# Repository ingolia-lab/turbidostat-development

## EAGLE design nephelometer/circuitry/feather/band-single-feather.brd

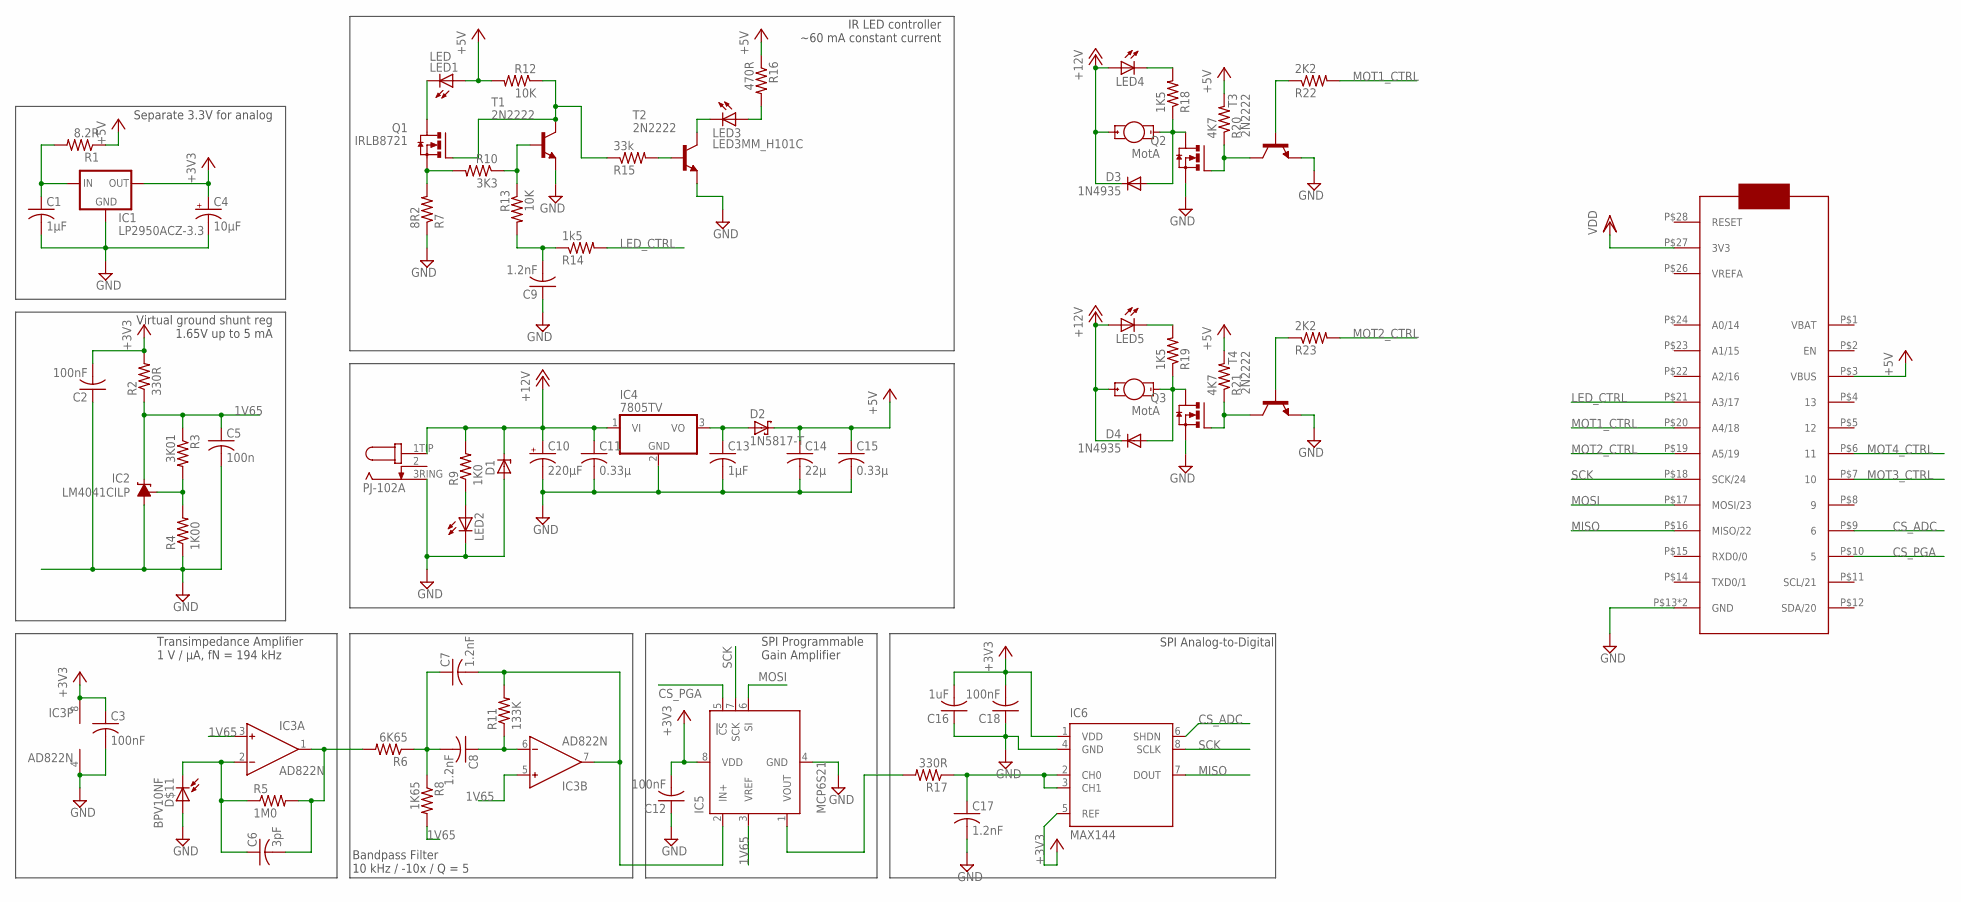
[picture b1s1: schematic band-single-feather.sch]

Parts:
C1, C13: 1µF; C025-030X050; DIGIKEY# 445-5318-ND
C2, C3, C12, C18: 100nF; C025-025X050; DIGIKEY# BC1084CT-ND
C4: 10µF; E2,5-5; DIGIKEY# 478-8042-1-ND
C5: 100n; C025-025X050; DIGIKEY# BC1084CT-ND
C6: 3pF; C025-024X044; DIGIKEY# 445-8377-ND
C7, C8, C9, C17: 1.2nF; C025-025X050; DIGIKEY# BC1026CT-ND
C10: 220µF; E3,5-8; DIGIKEY# P5166-ND
C11, C15: 0.33µ; C025-050X050; DIGIKEY# 445-5312-ND
C14: 22µ; C050-045X075; DIGIKEY# 445-8455-ND
C16: 1uF; C025-025X050; DIGIKEY# 445-5318-ND
D1: ZENER-DIODEF126-10; F126Z10; DIGIKEY# SA12ALFCT-ND
D2: 1N5817-T; DO41-7.6; DIGIKEY# 1N5817FSCT-ND
D3, D4: 1N4935; DO41-10; DIGIKEY# 1N4935FSCT-ND
D$11: BPV10NF; LED5MM; DIGIKEY# 751-1002-ND
IC1: LP2950ACZ-3.3; TO92; DIGIKEY# LP2950ACZ-3.3/NOPB-ND
IC2: LM4041CILP; LP_O-PBCY-W3; DIGIKEY# 296-22173-1-ND
IC3: AD822N; DIL08; DIGIKEY# AD823ANZ-ND
IC4: 7805TV; TO220V; DIGIKEY# LM7805CT-ND
IC5: MCP6S21; DIL08; DIGIKEY# MCP6S91-E/P-ND
IC6: MAX144; DIL08; DIGIKEY# MAX144ACPA+-ND
IC7: FEATHER_M0; DIGIKEY# 1528-1531-ND
J1: PJ-102A; DIGIKEY# CP-102A-ND
J2, J3: MotA; 1X02_3.5MM_MOT; DIGIKEY# ED2740-ND
LED1: LED; 1X02_3.5MM; DIGIKEY# 475-3002-ND
LED2: LED5MM; DIGIKEY# 754-1735-ND
LED3: LED3MM_H101C; DIGIKEY# 754-1727-ND
LED4, LED5: LED3MM; DIGIKEY# 754-1275-ND
Q1, Q2, Q3: IRLB8721; TO220BV; DIGIKEY# IRLB8721PBF-ND
R1: 8.2R; 0207/9; DIGIKEY# S8.2HCT-ND
R2: 330R; 0207/9; DIGIKEY# CF14JT330RCT-ND
R3: 3K01; 0207/9; DIGIKEY# RNF14FTD3K01CT-ND
R4: 1K00; 0207/9; DIGIKEY# RNF14FTD1K00CT-ND
R5: 1M0; 0207/9; DIGIKEY# RNV14FAL1M00CT-ND
R6: 6K65; 0207/9; DIGIKEY# 6.65KXBK-ND
R7: 8R2; 0207/9; DIGIKEY# S8.2HCT-ND
R8: 1K65; 0207/9; DIGIKEY# 1.65KXBK-ND
R9: 1K0; 0207/9; DIGIKEY# S1KHCT-ND
R10: 3K3; 0207/9; DIGIKEY# CF14JT3K30CT-ND
R11: 133K; 0207/9; DIGIKEY# 133KXBK-ND
R12, R13: 10K; 0207/9; DIGIKEY# CF14JT10K0CT-ND
R14: 1k5; 0207/9; DIGIKEY# CF14JT1K50CT-ND
R15: 33k; 0207/9; DIGIKEY# CF14JT33K0CT-ND
R16: 470R; 0207/5V; DIGIKEY# CF14JT470RCT-ND
R17: 330R; 0207/9; DIGIKEY# S330CACT-ND
R18, R19: 1K5; 0207/10; DIGIKEY# CF14JT1K50CT-ND
R20, R21: 4K7; 0207/10; DIGIKEY# CF14JT4K70CT-ND
R22, R23: 2K2; 0207/10; DIGIKEY# CF14JT2K20CT-ND
T1, T2, T3, T4: 2N2222; TO92-EBC-OVAL; DIGIKEY# PN2222ATFCT-ND

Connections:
1V65: C5.1, IC2.2 (C), IC3.3 (IN+), IC3.5 (IN+), IC5.3 (VREF), R2.1, R3.1, R8.2
+3V3: C2.2, C3.1, C4.+, C12.2, C16.2, C18.2, IC1.1 (OUT), IC3.8 (V+), IC5.8 (VDD), IC6.1 (VDD), IC6.5 (REF), R2.2
+5V: C14.1, C15.1, D2.C, IC7.P$3 (VBUS), LED1.1A (A), R1.1, R12.2, R16.1, R20.2, R21.2
+12V: C10.+, C11.1, D1.C, D3.C, D4.C, IC4.1 (VI), J1.1TIP (3TIP), J2.1A (+), J3.1A (+), LED4.A, LED5.A, R9.2
BPF: C7.2, IC3.7 (OUT), IC5.2 (IN+), R11.2
CS_ADC: IC6.6 (SHDN), IC7.P$9 (6)
CS_PGA: IC5.5 (!CS), IC7.P$10 (5)
FB: C6.1, D$11.K, IC3.2 (IN-), R5.1
GND: C1.2, C2.1, C3.2, C4.-, C5.2, C9.1, C10.-, C11.2, C12.1, C13.2, C14.2, C15.2, C16.1, C17.2, C18.1, D1.A, D$11.A, IC1.2 (GND), IC2.3 (A), IC3.4 (V-), IC4.2 (GND), IC5.4 (GND), IC6.4 (GND), IC7.P$13 (GND), IC7.P$25 (GND), J1.3RING (1RING), LED2.K (C), Q2.S, Q3.S, R4.1, R7.1, T1.E, T2.E, T3.E, T4.E
LED_CTRL: IC7.P$21 (A3/17), R14.2
MISO: IC6.7 (DOUT), IC7.P$16 (MISO/22)
MOSI: IC5.6 (SI), IC7.P$17 (MOSI/23)
MOT1: Q2.G, R20.1, T3.C
MOT1_CTRL: IC7.P$20 (A4/18), R22.2
MOT2: Q3.G, R21.1, T4.C
MOT2_CTRL: IC7.P$19 (A5/19), R23.2
MOT3_CTRL: IC7.P$7 (10)
MOT4_CTRL: IC7.P$6 (11)
unnamed: LED2.A, R9.1
unnamed: C7.1, C8.2, R6.1, R8.1
unnamed: IC5.1 (VOUT), R17.2
unnamed: D3.A, J2.2K (-), Q2.D, R18.1
unnamed: LED4.K (C), R18.2
unnamed: R22.1, T3.B
unnamed: Q1.G, R12.1, R15.1, T1.C
unnamed: C8.1, IC3.6 (IN-), R11.1
unnamed: D4.A, J3.2K (-), Q3.D, R19.1
unnamed: LED3.A, R16.2
unnamed: LED3.K, T2.C
unnamed: R10.1, R13.1, T1.B
unnamed: Q1.S, R7.2, R10.2
unnamed: C9.2, R13.2, R14.1
unnamed: R15.2, T2.B
unnamed: LED1.2K (K), Q1.D
unnamed: LED5.K (C), R19.2
unnamed: R23.1, T4.B
unnamed: C13.1, D2.A, IC4.3 (VO)
unnamed: C17.1, IC6.2 (CH0), IC6.3 (CH1), R17.1
unnamed: C1.1, IC1.3 (IN), R1.2
unnamed: IC2.1 (FB), R3.2, R4.2
SCK: IC5.7 (SCK), IC6.8 (SCLK), IC7.P$18 (SCK/24)
TIA: C6.2, IC3.1 (OUT), R5.2, R6.2
VDD: IC7.P$27 (3V3)

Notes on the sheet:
Transimpedance Amplifier 1 V / µA, fN = 194 kHz
Bandpass Filter 10 kHz / -10x / Q = 5
Virtual ground shunt reg 1.65V up to 5 mA
IR LED controller ~60 mA constant current
SPI Programmable Gain Amplifier
Separate 3.3V for analog
SPI Analog-to-Digital

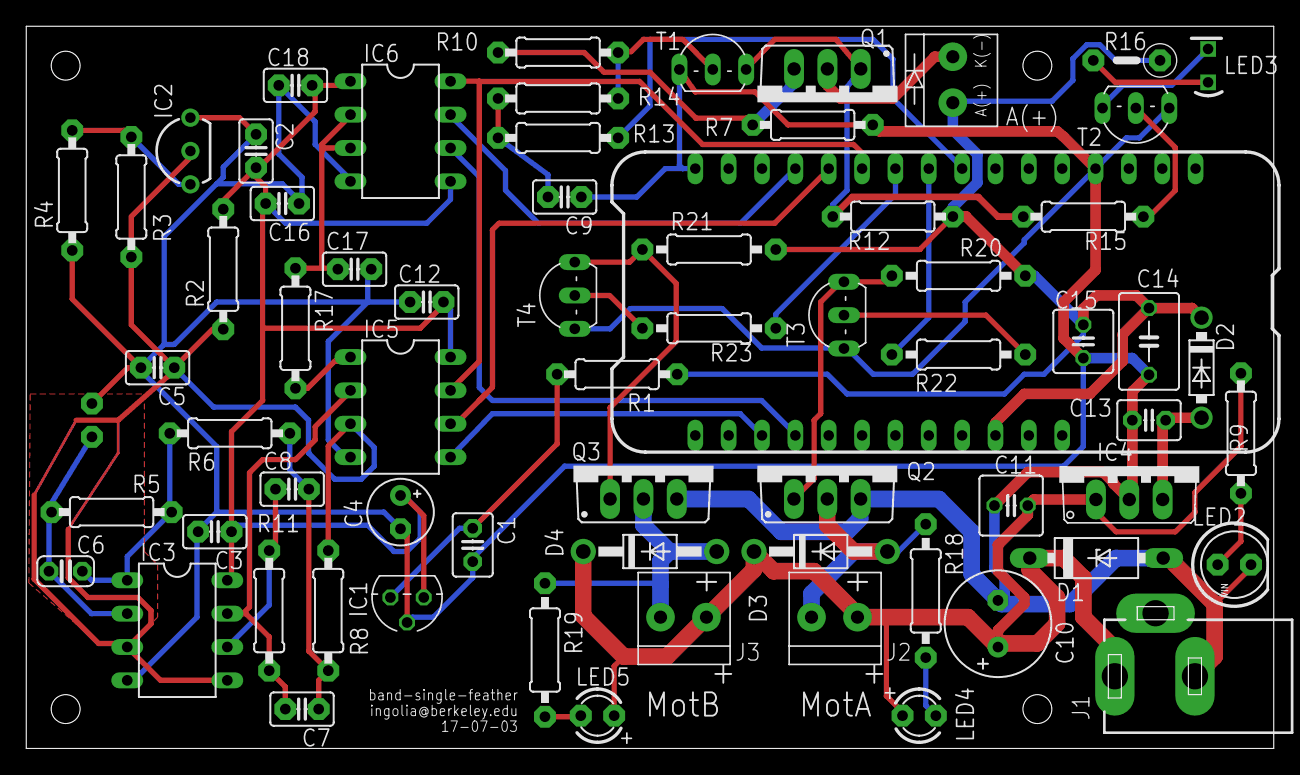
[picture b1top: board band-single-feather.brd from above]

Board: 2 copper layers, 95.0 x 55.0 mm, 72 parts (1 on the bottom side), 40 nets.

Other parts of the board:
U$1, U$2, U$3, U$4: M2MOUNT

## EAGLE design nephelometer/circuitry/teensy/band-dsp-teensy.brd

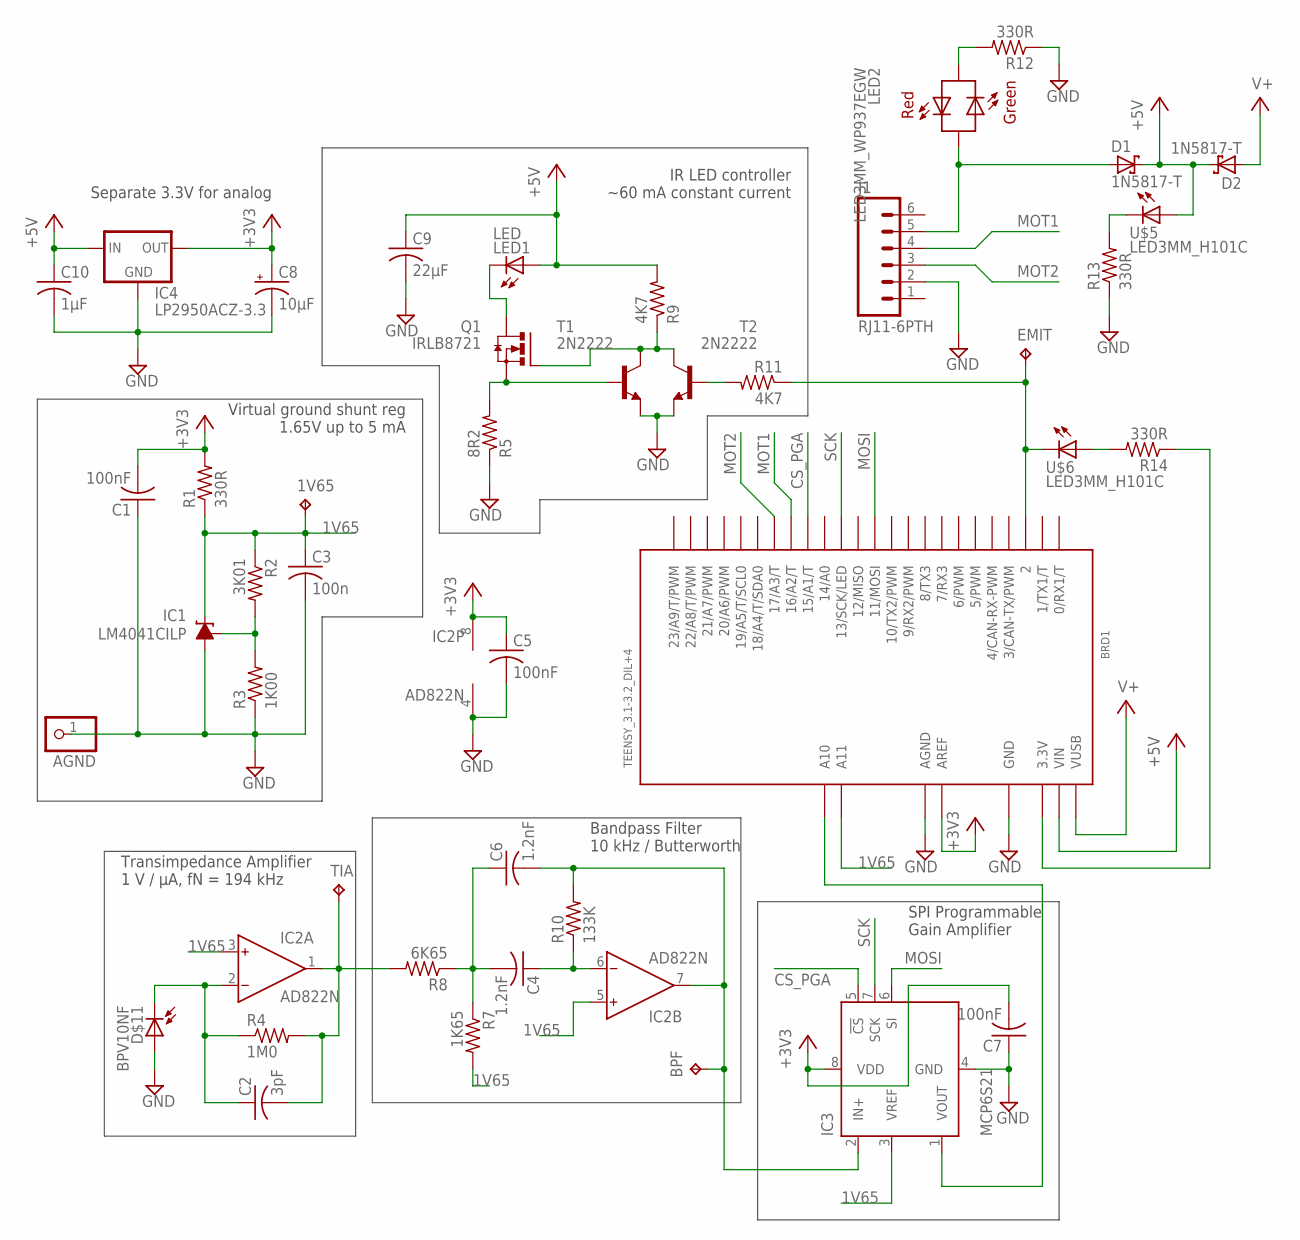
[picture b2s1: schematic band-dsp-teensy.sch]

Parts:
1V65: TPTP10R; TP10R
AGND: PINHD-1X1; 1X01
BPF: TPTP10R; TP10R
BRD1: TEENSY_3.1-3.2_DIL+4; TEENSY_3.0-3.2&LC_DIL+4; DIGIKEY# 1568-1231-ND
C1, C5, C7: 100nF; C025-025X050; DIGIKEY# BC1084CT-ND
C2: 3pF; C025-024X044; DIGIKEY# 445-8377-ND
C3: 100n; C025-025X050; DIGIKEY# BC1084CT-ND
C4, C6: 1.2nF; C025-025X050; DIGIKEY# BC1026CT-ND
C8: 10µF; E2,5-5; DIGIKEY# 478-8042-1-ND
C9: 22µF; C050-045X075; DIGIKEY# 445-8455-ND
C10: 1µF; C025-030X050; DIGIKEY# 445-5318-ND
D1, D2: 1N5817-T; DO41-7.6; DIGIKEY# 1N5817FSCT-ND
D$11: BPV10NF; LED5MM; DIGIKEY# 751-1002-ND
EMIT: TPPAD1-13; P1-13
IC1: LM4041CILP; LP_O-PBCY-W3; DIGIKEY# 296-22173-1-ND
IC2: AD822N; DIL08; DIGIKEY# AD823ANZ-ND
IC3: MCP6S21; DIL08; DIGIKEY# MCP6S91-E/P-ND
IC4: LP2950ACZ-3.3; TO92; DIGIKEY# LP2950ACZ-3.3/NOPB-ND
J1: RJ11-6PTH; RJ11-6; DIGIKEY# AE10383-ND
LED1: LED; 1X02_3.5MM; DIGIKEY# 475-3002-ND
LED2: LED3MM_WP937EGW; LED3MM_H101C_BICOL; DIGIKEY# 754-1751-ND
Q1: IRLB8721; TO220BH; DIGIKEY# IRLB8721PBF-ND
R1, R12, R13: 330R; 0207/9; DIGIKEY# CF14JT330RCT-ND
R2: 3K01; 0207/9; DIGIKEY# RNF14FTD3K01CT-ND
R3: 1K00; 0207/9; DIGIKEY# RNF14FTD1K00CT-ND
R4: 1M0; 0207/9; DIGIKEY# RNV14FAL1M00CT-ND
R5: 8R2; 0207/9; DIGIKEY# S8.2HCT-ND
R7: 1K65; 0207/9; DIGIKEY# 1.65KXBK-ND
R8: 6K65; 0207/9; DIGIKEY# 6.65KXBK-ND
R9, R11: 4K7; 0207/9; DIGIKEY# CF14JT4K70CT-ND
R10: 133K; 0207/9; DIGIKEY# 133KXBK-ND
R14: 330R; 0207/9; DIGIKEY# CF14JT150RCT-ND
T1, T2: 2N2222; TO92-EBC-OVAL; DIGIKEY# PN2222ATFCT-ND
TIA: TPTP10R; TP10R
U$5: LED3MM_H101C; DIGIKEY# 754-1595-ND
U$6: LED3MM_H101C; DIGIKEY# 754-1727-ND

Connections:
1V65: 1V65.TP, BRD1.A11, C3.1, IC1.2 (C), IC2.3 (IN+), IC2.5 (IN+), IC3.3 (VREF), R1.1, R2.1, R7.2
+3V3: BRD1.AREF, C1.2, C5.1, C7.2, C8.+, IC2.8 (V+), IC3.8 (VDD), IC4.1 (OUT), R1.2
+5V: BRD1.VIN, C9.1, C10.1, D1.C, D2.C, IC4.3 (IN), LED1.1A (A), R9.2, U$5.A
CS_PGA: BRD1.15/A1 (15/A1/T), IC3.5 (!CS)
GND: AGND.1, BRD1.AGND, BRD1.GND, C1.1, C3.2, C5.2, C7.1, C8.-, C9.2, C10.2, D$11.A, IC1.3 (A), IC2.4 (V-), IC3.4 (GND), IC4.2 (GND), J1.2, R3.1, R5.1, R12.1, R13.1, T1.E, T2.E
LEDCTRL: R11.2, T2.B
MOSI: BRD1.11 (11/MOSI), IC3.6 (SI)
MOT1: BRD1.16/A2 (16/A2/T), J1.4
MOT2: BRD1.17/A3 (17/A3/T), J1.3
unnamed: C2.1, D$11.K, IC2.2 (IN-), R4.1
unnamed: BRD1.3.3V, R14.1
unnamed: C4.2, C6.1, R7.1, R8.1
unnamed: BRD1.A10, IC3.1 (VOUT)
unnamed: BRD1.2, EMIT.TP, R11.1, U$6.K
unnamed: BPF.TP, C6.2, IC2.7 (OUT), IC3.2 (IN+), R10.2
unnamed: R13.2, U$5.K
unnamed: Q1.G, R9.1, T1.C, T2.C
unnamed: C4.1, IC2.6 (IN-), R10.1
unnamed: D1.A, J1.5, LED2.SHORT (GA)
unnamed: R14.2, U$6.A
unnamed: LED2.LONG (GK), R12.2
unnamed: Q1.S, R5.2, T1.B
unnamed: LED1.2K (K), Q1.D
unnamed: C2.2, IC2.1 (OUT), R4.2, R8.2, TIA.TP
unnamed: IC1.1 (FB), R2.2, R3.2
SCK: BRD1.13 (13/SCK/LED), IC3.7 (SCK)
V+: BRD1.VUSB, D2.A

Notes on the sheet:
Transimpedance Amplifier 1 V / µA, fN = 194 kHz
Bandpass Filter 10 kHz / Butterworth
Virtual ground shunt reg 1.65V up to 5 mA
IR LED controller ~60 mA constant current
SPI Programmable Gain Amplifier
Separate 3.3V for analog

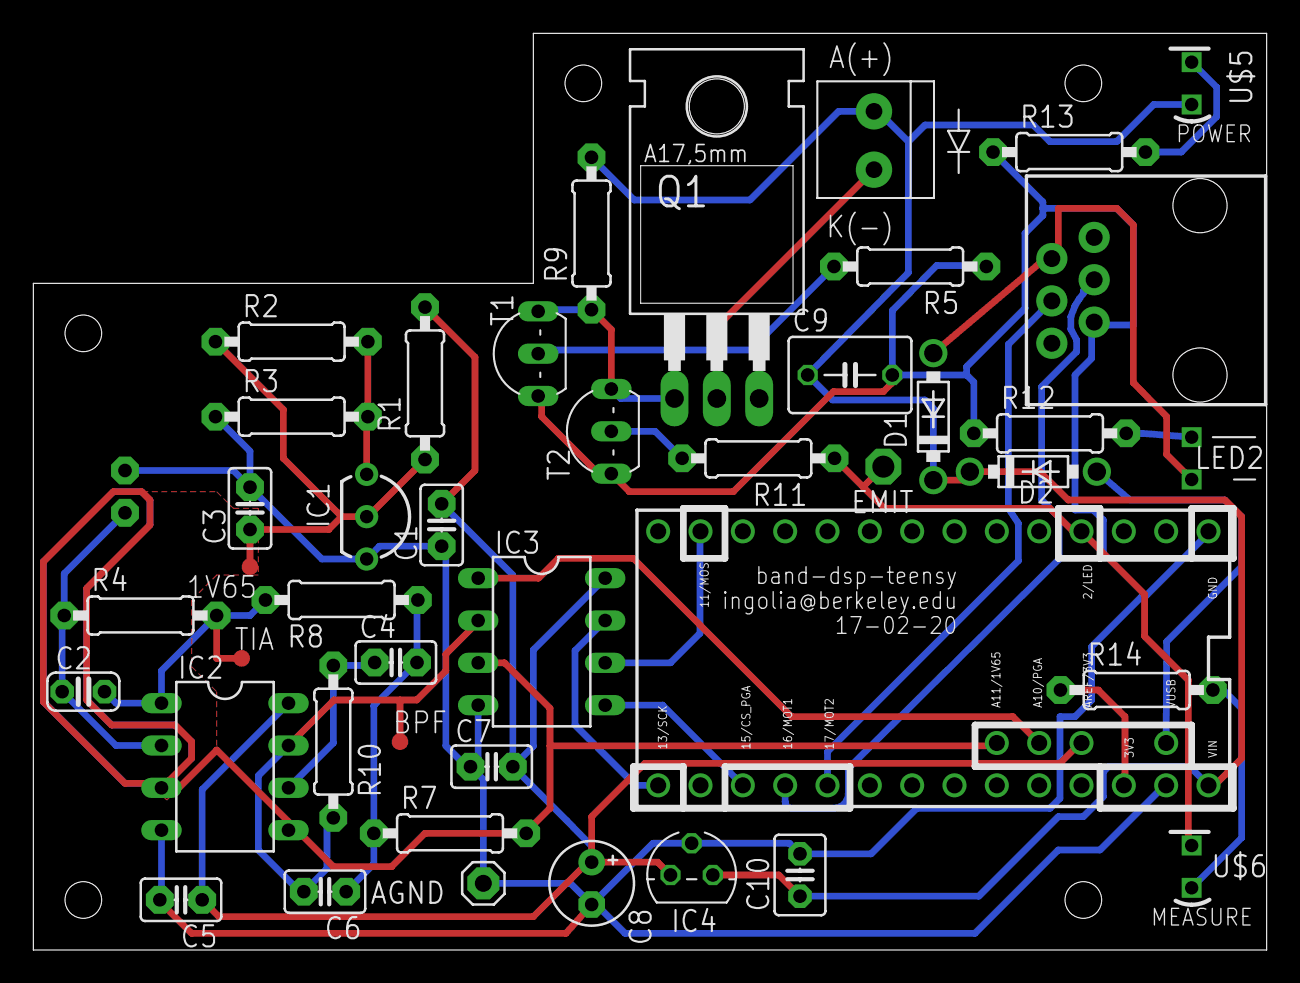
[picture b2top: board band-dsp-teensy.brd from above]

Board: 2 copper layers, 74.0 x 55.0 mm, 49 parts (1 on the bottom side), 27 nets.

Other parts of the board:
U$1, U$2, U$3, U$4, U$7: M2MOUNT

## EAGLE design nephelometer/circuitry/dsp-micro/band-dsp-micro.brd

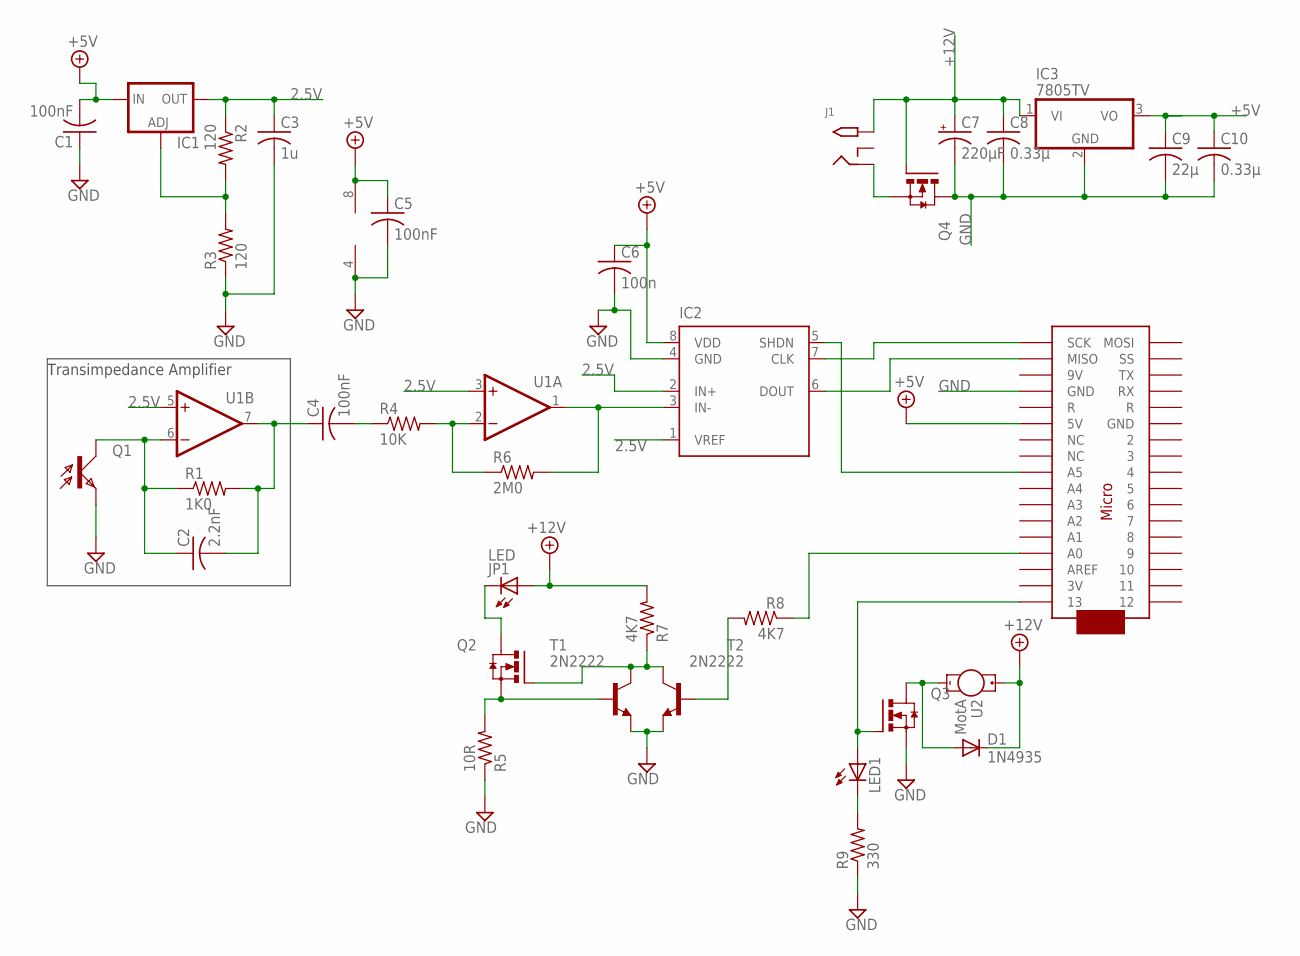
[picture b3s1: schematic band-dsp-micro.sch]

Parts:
C1, C5: 100nF; C025-025X050; DIGIKEY# BC1084CT-ND
C2: 2.2nF; C025-024X044; DIGIKEY# BC1029CT-ND
C3: 1u; C050-024X044; DIGIKEY# 445-8614-ND
C4: 100nF; C025-060X050; DIGIKEY# 445-8325-ND
C6: 100n; C025-025X050; DIGIKEY# BC1084CT-ND
C7: 220µF; E3,5-8; DIGIKEY# P5166-ND
C8, C10: 0.33µ; C025-050X050; DIGIKEY# 445-5312-ND
C9: 22µ; C050-045X075; DIGIKEY# 445-8455-ND
D1: 1N4935; DO41-10; DIGIKEY# 1N4935FSCT-ND
IC1: LM317L; 317L; DIGIKEY# 296-33312-5-ND
IC2: MCP3301; DIL08; DIGIKEY# MCP3301-BI/P-ND
IC3: 7805TV; TO220V; DIGIKEY# LM7805CT-ND
J1: 2.1MMJACKTHM; PJ-102A; DIGIKEY# CP-102A-ND
JP1: LED; 1X02_SCREW; DIGIKEY# 475-3002-ND
LED1: LED3MM; DIGIKEY# 160-1139-ND
Q1: LTR-4206; 3MM_LED; DIGIKEY# 160-1030-ND
Q2, Q3, Q4: IRLB8721; TO220BV; DIGIKEY# IRLB8721PBF-ND
R1: 1K0; 0204/5; DIGIKEY# S1KCACT-ND
R2, R3: 120; 0204V; DIGIKEY# S120CACT-ND
R4: 10K; 0204/5; DIGIKEY# S10KCACT-ND
R5: 10R; 0204V; DIGIKEY# PPC10W-1CT-ND
R6: 2M0; 0309V; DIGIKEY# RNV14FAL2M00TB-ND
R7, R8: 4K7; 0204V; DIGIKEY# S4.7KQCT-ND
R9: 330; 0204V; DIGIKEY# CF14JT330RCT-ND
T1, T2: 2N2222; TO92-EBC-OVAL; DIGIKEY# PN2222ATFCT-ND
U1: LMC6482; DIL08; DIGIKEY# LMC6482AIN/NOPB-ND
U2: MotA; 1X02_SCREW; DIGIKEY# SC1455-ND
U3: ARDUINOMICRO; DIGIKEY# 1050-1066-ND

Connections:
2.5V: C3.1, IC1.2 (OUT), IC2.1 (VREF), IC2.2 (IN+), R2.1, U1.3 (+IN), U1.5 (+IN)
+5V: C1.2, C5.1, C6.1, C9.1, C10.1, IC1.3 (IN), IC2.8 (VDD), IC3.3 (VO), U1.8 (V+), U3.P$23 (5V)
+12V: C7.+, C8.1, D1.C, IC3.1 (VI), J1.TIP, JP1.1/POS (A), Q4.G, R7.2, U2.1/POS (+)
GND: C1.1, C3.2, C5.2, C6.2, C7.-, C8.2, C9.2, C10.2, IC2.4 (GND), IC3.2 (GND), Q1.A (E), Q3.S, Q4.D, R3.1, R5.1, R9.1, T1.E, T2.E, U1.4 (V-), U3.P$12 (GND)
LEDCTRL: R8.2, T2.B
unnamed: C2.1, Q1.K (C), R1.1, U1.6 (-IN)
unnamed: C4.2, R4.1
unnamed: D1.A, Q3.D, U2.2 (-)
unnamed: IC2.6 (DOUT), U3.P$19 (MISO)
unnamed: R8.1, U3.P$31 (A0)
unnamed: IC2.7 (CLK), U3.P$18 (SCK)
unnamed: IC2.5 (SHDN), U3.P$26 (A5)
unnamed: Q2.G, R7.1, T1.C, T2.C
unnamed: Q2.S, R5.2, T1.B
unnamed: LED1.K (C), R9.2
unnamed: JP1.2 (K), Q2.D
unnamed: LED1.A, Q3.G, U3.P$34 (13)
unnamed: C2.2, C4.1, R1.2, U1.7 (OUT)
unnamed: R4.2, R6.1, U1.2 (-IN)
unnamed: IC2.3 (IN-), R6.2, U1.1 (OUT)
unnamed: IC1.1 (ADJ), R2.2, R3.2
unnamed: J1.RING, Q4.S

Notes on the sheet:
Transimpedance Amplifier

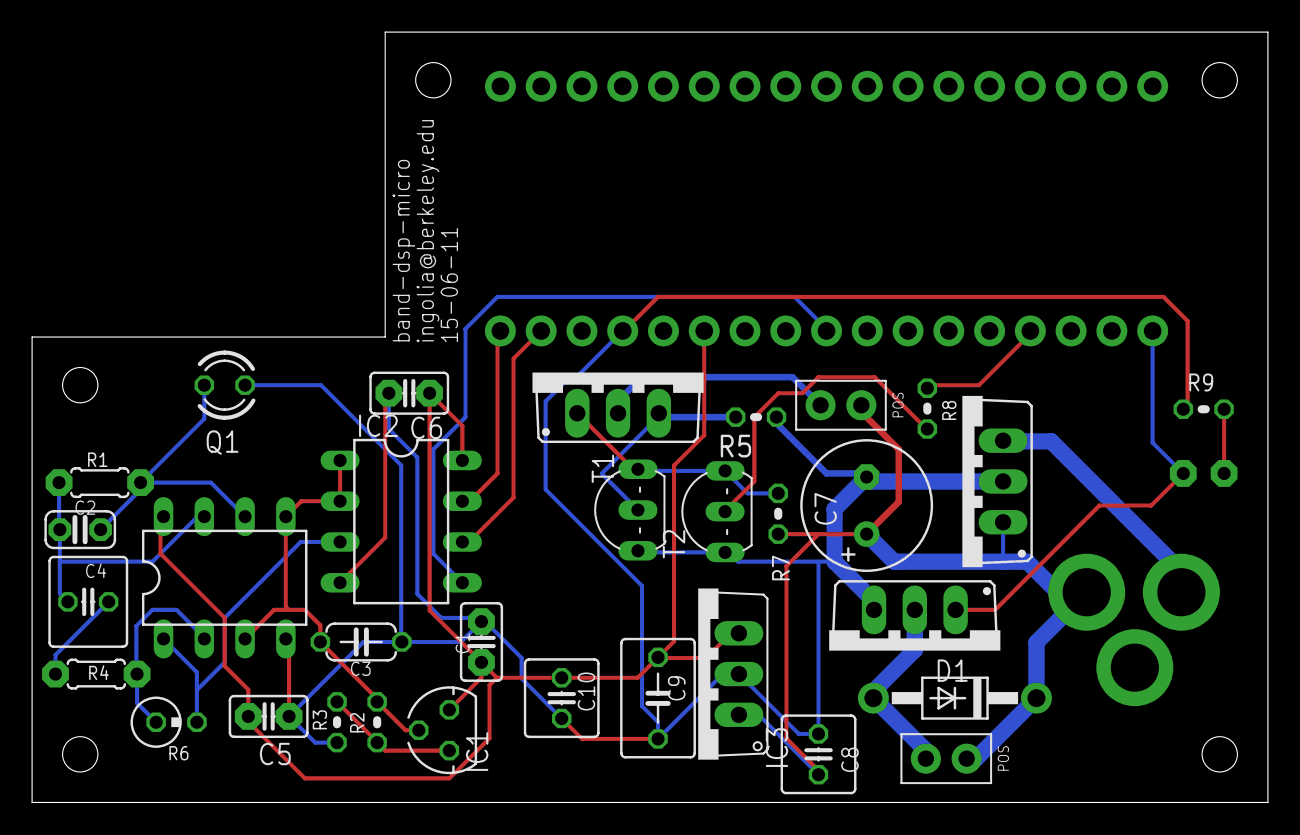
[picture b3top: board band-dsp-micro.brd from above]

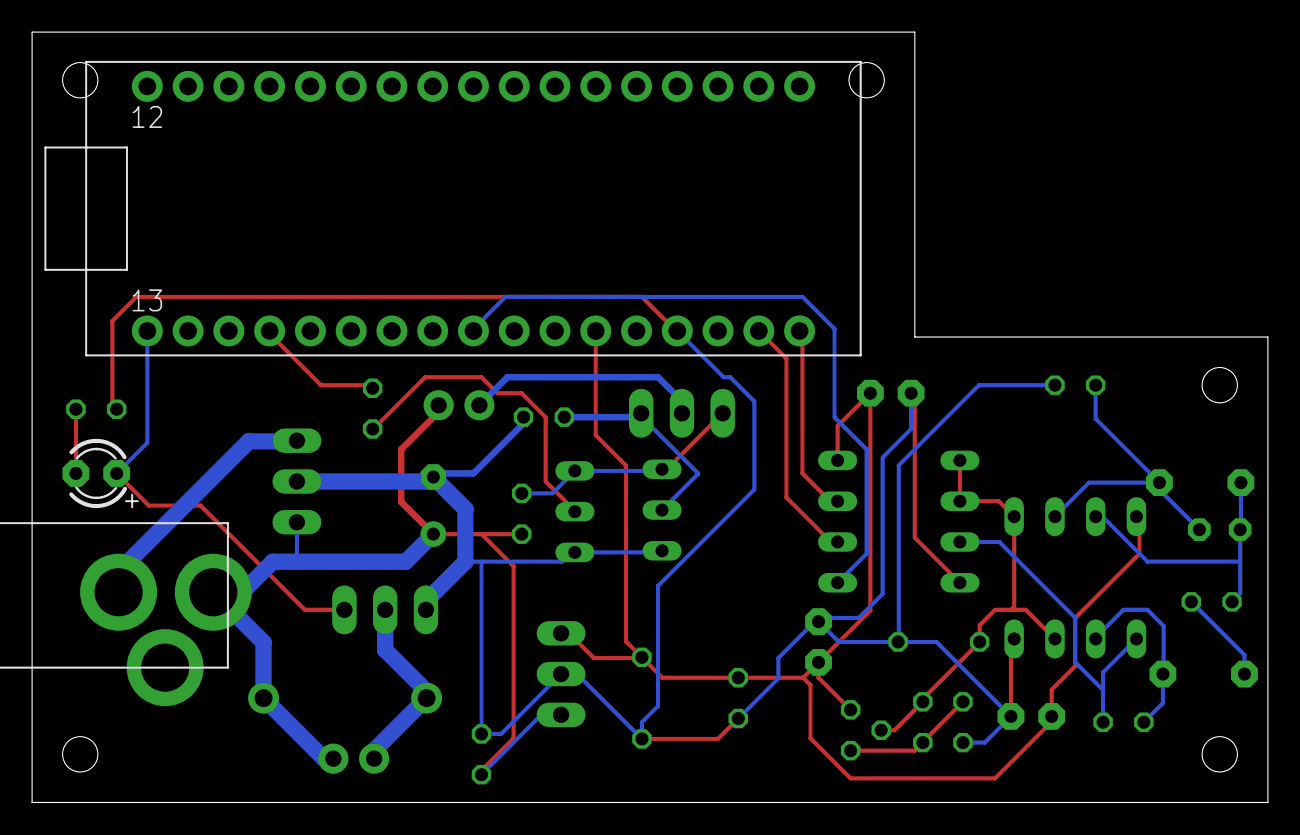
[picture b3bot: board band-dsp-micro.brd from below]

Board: 2 copper layers, 77.0 x 48.0 mm, 40 parts (3 on the bottom side), 22 nets.

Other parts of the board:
U$1, U$2, U$3, U$4, U$7: M2MOUNT

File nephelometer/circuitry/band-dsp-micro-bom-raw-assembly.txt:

C1	100nF	BC1084CT-ND	Vishay BC Components	K104K15X7RF5TL2
C2	2.2nF	BC1029CT-ND	Vishay BC Components	K222J15C0GF5TL2
C3	1u	445-8614-ND	TDK Corporation	FK28X7R1C105K
C4	100nF	445-8325-ND	TDK Corporation	FK16C0G1H104J
C5	100nF	BC1084CT-ND		
C6	100n	BC1084CT-ND		
C7	220µF	P5166-ND	Panasonic Electronic Components	ECA-1VM221
C8	0.33µ	445-5312-ND 	TDK Corporation	FK14X7R1H334K
C9	22µ	445-8455-ND	TDK Corporation	FK20X7R1C226M
C10	0.33µ	445-5312-ND 	TDK Corporation	FK14X7R1H334K
D1	1N4935	1N4935FSCT-ND	Fairchild Semiconductor	1N4935
IC1		296-33312-5-ND	Texas Instruments	LM317LCLP
IC2		MCP3301-BI/P-ND	Microchip Technology	MCP3301-BI/P
IC2		AE9986-ND		
IC3	7805TV	LM7805CT-ND 	Fairchild Semiconductor	LM7805CT
J1	2.1MMJACKTHM	CP-102A-ND 	CUI Inc	PJ-102A
J1	2.1MMJACKTHM	T1071-P5P-ND 	CUI Inc	EPSA120200U-P5P-SZ
JP1	LED	475-3002-ND	OSRAM Opto Semiconductors Inc	SFH 4547
JP1	LED	492-1502-ND	Bivar Inc	CR-174
LED1		160-1139-ND	Lite-On Inc	LTL-4221N
Q1		160-1030-ND	Lite-On Inc	LTR-4206E
Q2		IRLB8721PBF-ND		
Q3		IRLB8721PBF-ND	International Rectifier	IRLB8721PBF
Q4		IRLB8721PBF-ND	International Rectifier	IRLB8721PBF
R1	1K0	S1KCACT-ND 	Stackpole Electronics Inc	RNMF14FTC1K00
R2	120	S120CACT-ND	Stackpole Electronics Inc	RNMF14FTC120R
R3	120	S120CACT-ND	Stackpole Electronics Inc	RNMF14FTC120R
R4	10K	S10KCACT-ND 	Stackpole Electronics Inc	RNMF14FTC10K0
R5	10R	PPC10W-1CT-ND	Vishay BC Components	PR01000101009JR500
R6	2M0	RNV14FAL2M00TB-ND	Stackpole Electronics Inc	RNV14FAL2M00
R7	4K7	S4.7KQCT-ND	Stackpole Electronics Inc	CFM14JT4K70
R8	4K7	S4.7KQCT-ND	Stackpole Electronics Inc	CFM14JT4K70
R9	330	CF14JT330RCT-ND 	Stackpole Electronics Inc	CF14JT330R
T1	2N2222	PN2222ATFCT-ND	Fairchild Semiconductor	PN2222ATF
T2	2N2222	PN2222ATFCT-ND	Fairchild Semiconductor	PN2222ATF
U1		LMC6482AIN/NOPB-ND	Texas Instruments	LMC6482AIN/NOPB
U1		AE9986-ND		
U2	MotA	SC1455-ND	Switchcraft Inc.	35PM1
U3		1050-1066-ND	Arduino	A000053
U3		S7050-ND	Sullins Connector Solutions	PPPC171LFBN-RC
U3		S7050-ND	Sullins Connector Solutions	PPPC171LFBN-RC
U3		AE10419-ND	Assmann WSW Components	AK67421-1

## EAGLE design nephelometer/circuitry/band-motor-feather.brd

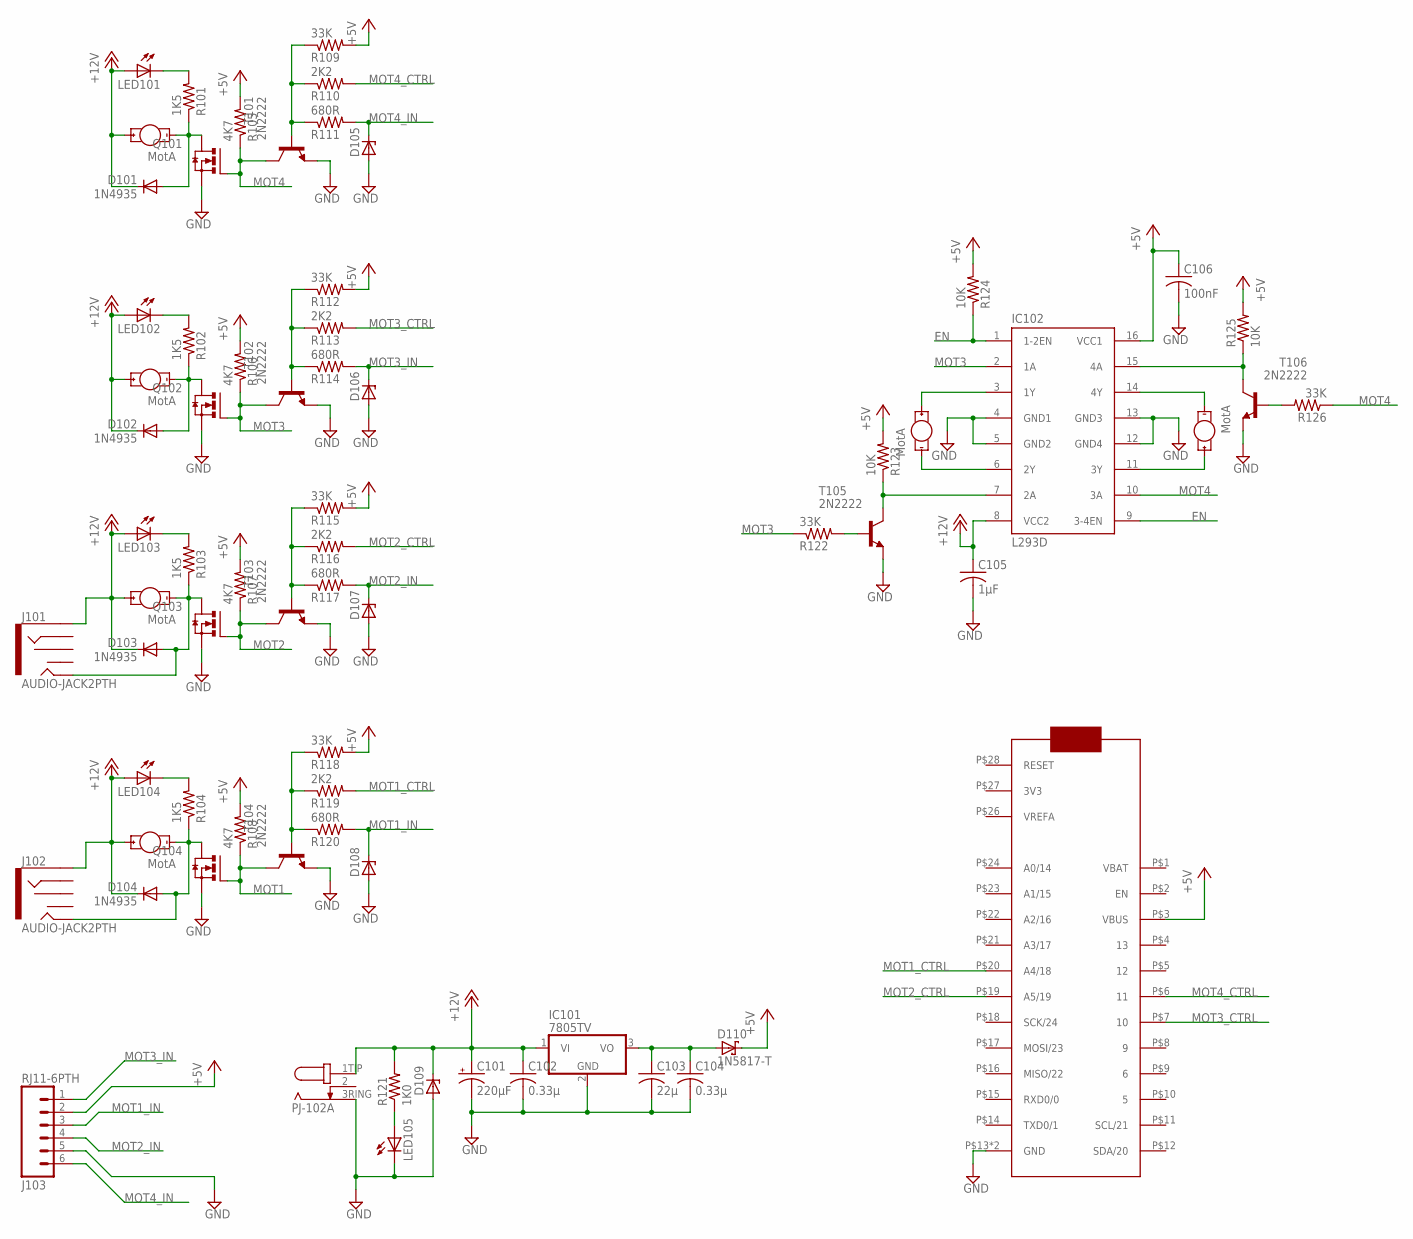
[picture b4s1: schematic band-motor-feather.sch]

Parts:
C101: 220µF; E3,5-8; DIGIKEY# P5166-ND
C102, C104: 0.33µ; C025-050X050; DIGIKEY# 445-5312-ND
C103: 22µ; C050-045X075; DIGIKEY# 445-8455-ND
C105: 1µF; C025-025X050; DIGIKEY# 445-5318-ND
C106: 100nF; C025-025X050; DIGIKEY# BC1084CT-ND
D101, D102, D103, D104: 1N4935; DO41-10; DIGIKEY# 1N4935FSCT-ND
D105, D106, D107, D108: ZENER-DIODEF126-10; F126Z10; DIGIKEY# SA5.0ALFCT-ND
D109: ZENER-DIODEF126-10; F126Z10; DIGIKEY# SA12ALFCT-ND
D110: 1N5817-T; DO41-7.6; DIGIKEY# 1N5817FSCT-ND
IC101: 7805TV; TO220V; DIGIKEY# LM7805CT-ND
IC102: L293D; DIL16; DIGIKEY# 296-9518-5-ND
IC103: FEATHER_M0; DIGIKEY# 2830-ND
J101, J102: AUDIO-JACK2PTH; AUDIO-JACK; DIGIKEY# CP1-3523N-ND
J103: RJ11-6PTH; RJ11-6; DIGIKEY# AE10383-ND
J104, J105, J106, J107, J109, J110: MotA; 1X02_3.5MM_MOT; DIGIKEY# ED2740-ND
J108: PJ-102A; DIGIKEY# CP-102A-ND
LED101, LED102, LED103, LED104: LED3MM; DIGIKEY# 754-1275-ND
LED105: LED5MM; DIGIKEY# 754-1735-ND
Q101, Q102, Q103, Q104: IRLB8721; TO220BV; DIGIKEY# IRLB8721PBF-ND
R101, R102, R103, R104: 1K5; 0207/10; DIGIKEY# CF14JT1K50CT-ND
R105, R106, R107, R108: 4K7; 0207/10; DIGIKEY# CF14JT4K70CT-ND
R109, R112, R115, R118, R122, R126: 33K; 0207/10; DIGIKEY# CF14JT33K0CT-ND
R110, R113, R116, R119: 2K2; 0207/10; DIGIKEY# CF14JT2K20CT-ND
R111, R114, R117, R120: 680R; 0207/10; DIGIKEY# CF14JT680RCT-ND
R121: 1K0; 0207/9; DIGIKEY# S1KHCT-ND
R123, R124, R125: 10K; 0207/10; DIGIKEY# CF14JT10K0CT-ND
T101, T102, T103, T104, T105, T106: 2N2222; TO92-EBC-OVAL; DIGIKEY# PN2222ATFCT-ND

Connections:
+5V: C106.1, D110.C, IC102.16 (VCC1), IC103.P$3 (VBUS), J103.2, R105.2, R106.2, R107.2, R108.2, R109.2, R112.2, R115.2, R118.2, R123.2, R124.2, R125.2
+12V: C101.+, C102.1, C105.1, D101.C, D102.C, D103.C, D104.C, D109.C, IC101.1 (VI), IC102.8 (VCC2), J101.SLEEVE, J102.SLEEVE, J104.1A (+), J105.1A (+), J106.1A (+), J107.1A (+), J108.1TIP (3TIP), LED101.A, LED102.A, LED103.A, LED104.A, R121.2
EN: IC102.1 (1-2EN), IC102.9 (3-4EN), R124.1
GND: C101.-, C102.2, C103.2, C104.2, C105.2, C106.2, D105.A, D106.A, D107.A, D108.A, D109.A, IC101.2 (GND), IC102.4 (GND1), IC102.5 (GND2), IC102.12 (GND4), IC102.13 (GND3), IC103.P$13 (GND), IC103.P$25 (GND), J103.5, J108.3RING (1RING), LED105.K (C), Q101.S, Q102.S, Q103.S, Q104.S, T101.E, T102.E, T103.E, T104.E, T105.E, T106.E
MOT1: Q104.G, R108.1, T104.C
MOT1_CTRL: IC103.P$20 (A4/18), R119.2
MOT1_IN: D108.C, J103.3, R120.2
MOT2: Q103.G, R107.1, T103.C
MOT2_CTRL: IC103.P$19 (A5/19), R116.2
MOT2_IN: D107.C, J103.4, R117.2
MOT3: IC102.2 (1A), Q102.G, R106.1, R122.1, T102.C
MOT3_CTRL: IC103.P$7 (10), R113.2
MOT3_IN: D106.C, J103.1, R114.2
MOT4: IC102.10 (3A), Q101.G, R105.1, R126.1, T101.C
MOT4_CTRL: IC103.P$6 (11), R110.2
MOT4_IN: D105.C, J103.6, R111.2
unnamed: LED105.A, R121.1
unnamed: C103.1, C104.1, D110.A, IC101.3 (VO)
unnamed: D103.A, J101.TIP, J106.2K (-), Q103.D, R103.1
unnamed: D104.A, J102.TIP, J107.2K (-), Q104.D, R104.1
unnamed: LED104.K (C), R104.2
unnamed: R118.1, R119.1, R120.1, T104.B
unnamed: LED103.K (C), R103.2
unnamed: R112.1, R113.1, R114.1, T102.B
unnamed: R109.1, R110.1, R111.1, T101.B
unnamed: R115.1, R116.1, R117.1, T103.B
unnamed: IC102.15 (4A), R125.1, T106.C
unnamed: R126.2, T106.B
unnamed: IC102.7 (2A), R123.1, T105.C
unnamed: R122.2, T105.B
unnamed: IC102.3 (1Y), J109.1A (+)
unnamed: IC102.6 (2Y), J109.2K (-)
unnamed: IC102.14 (4Y), J110.2K (-)
unnamed: IC102.11 (3Y), J110.1A (+)
unnamed: D102.A, J105.2K (-), Q102.D, R102.1
unnamed: LED102.K (C), R102.2
unnamed: D101.A, J104.2K (-), Q101.D, R101.1
unnamed: LED101.K (C), R101.2

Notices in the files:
parts and their libraries:
SparkFun-Connectors: Licensing: CC v3.0 Share-Alike You are welcome to use this library for commercial purposes.
